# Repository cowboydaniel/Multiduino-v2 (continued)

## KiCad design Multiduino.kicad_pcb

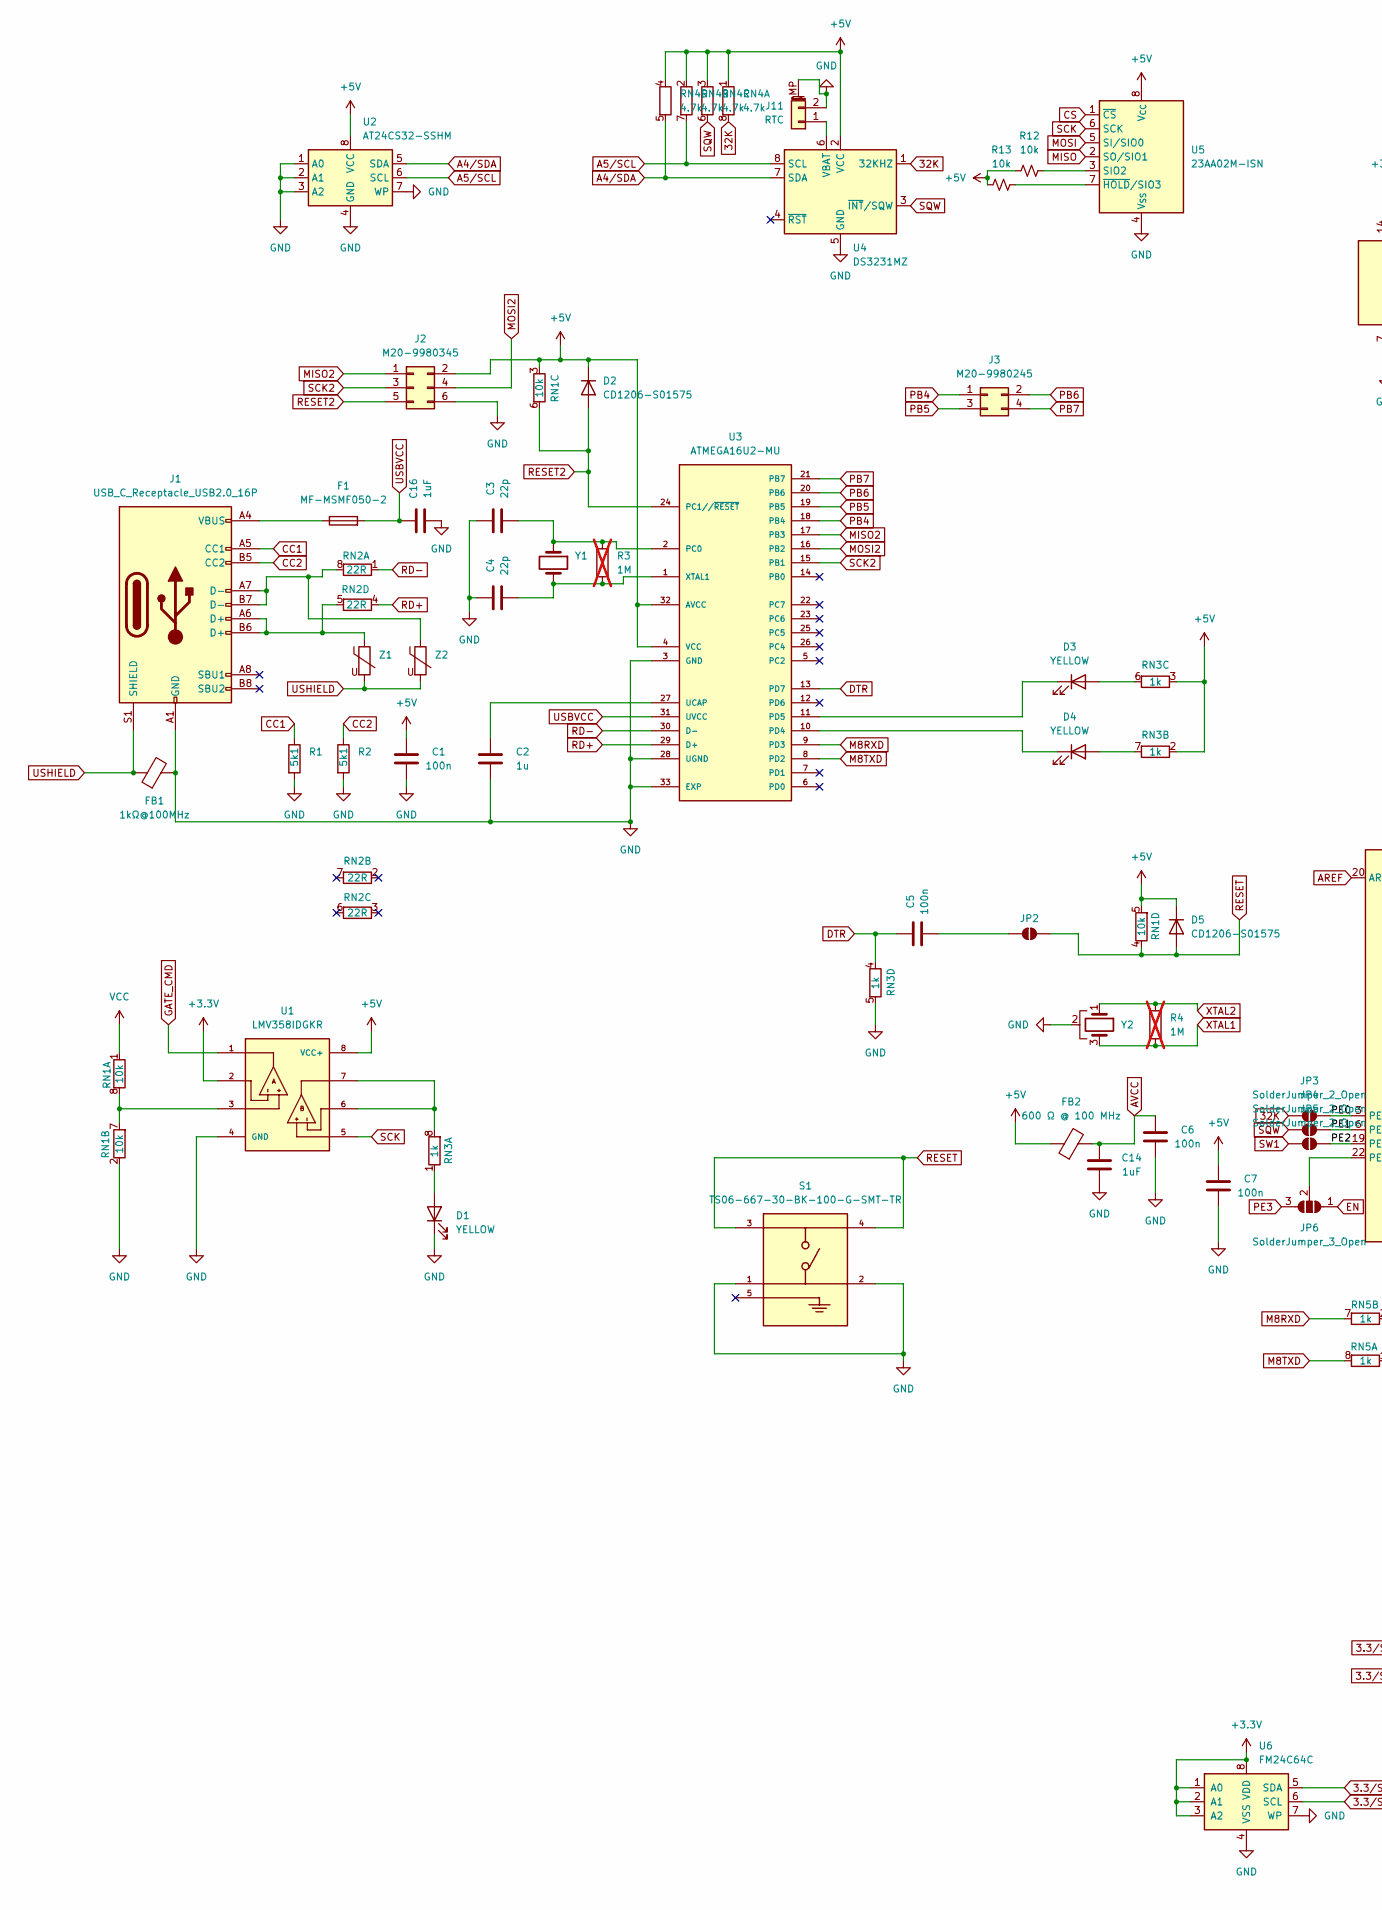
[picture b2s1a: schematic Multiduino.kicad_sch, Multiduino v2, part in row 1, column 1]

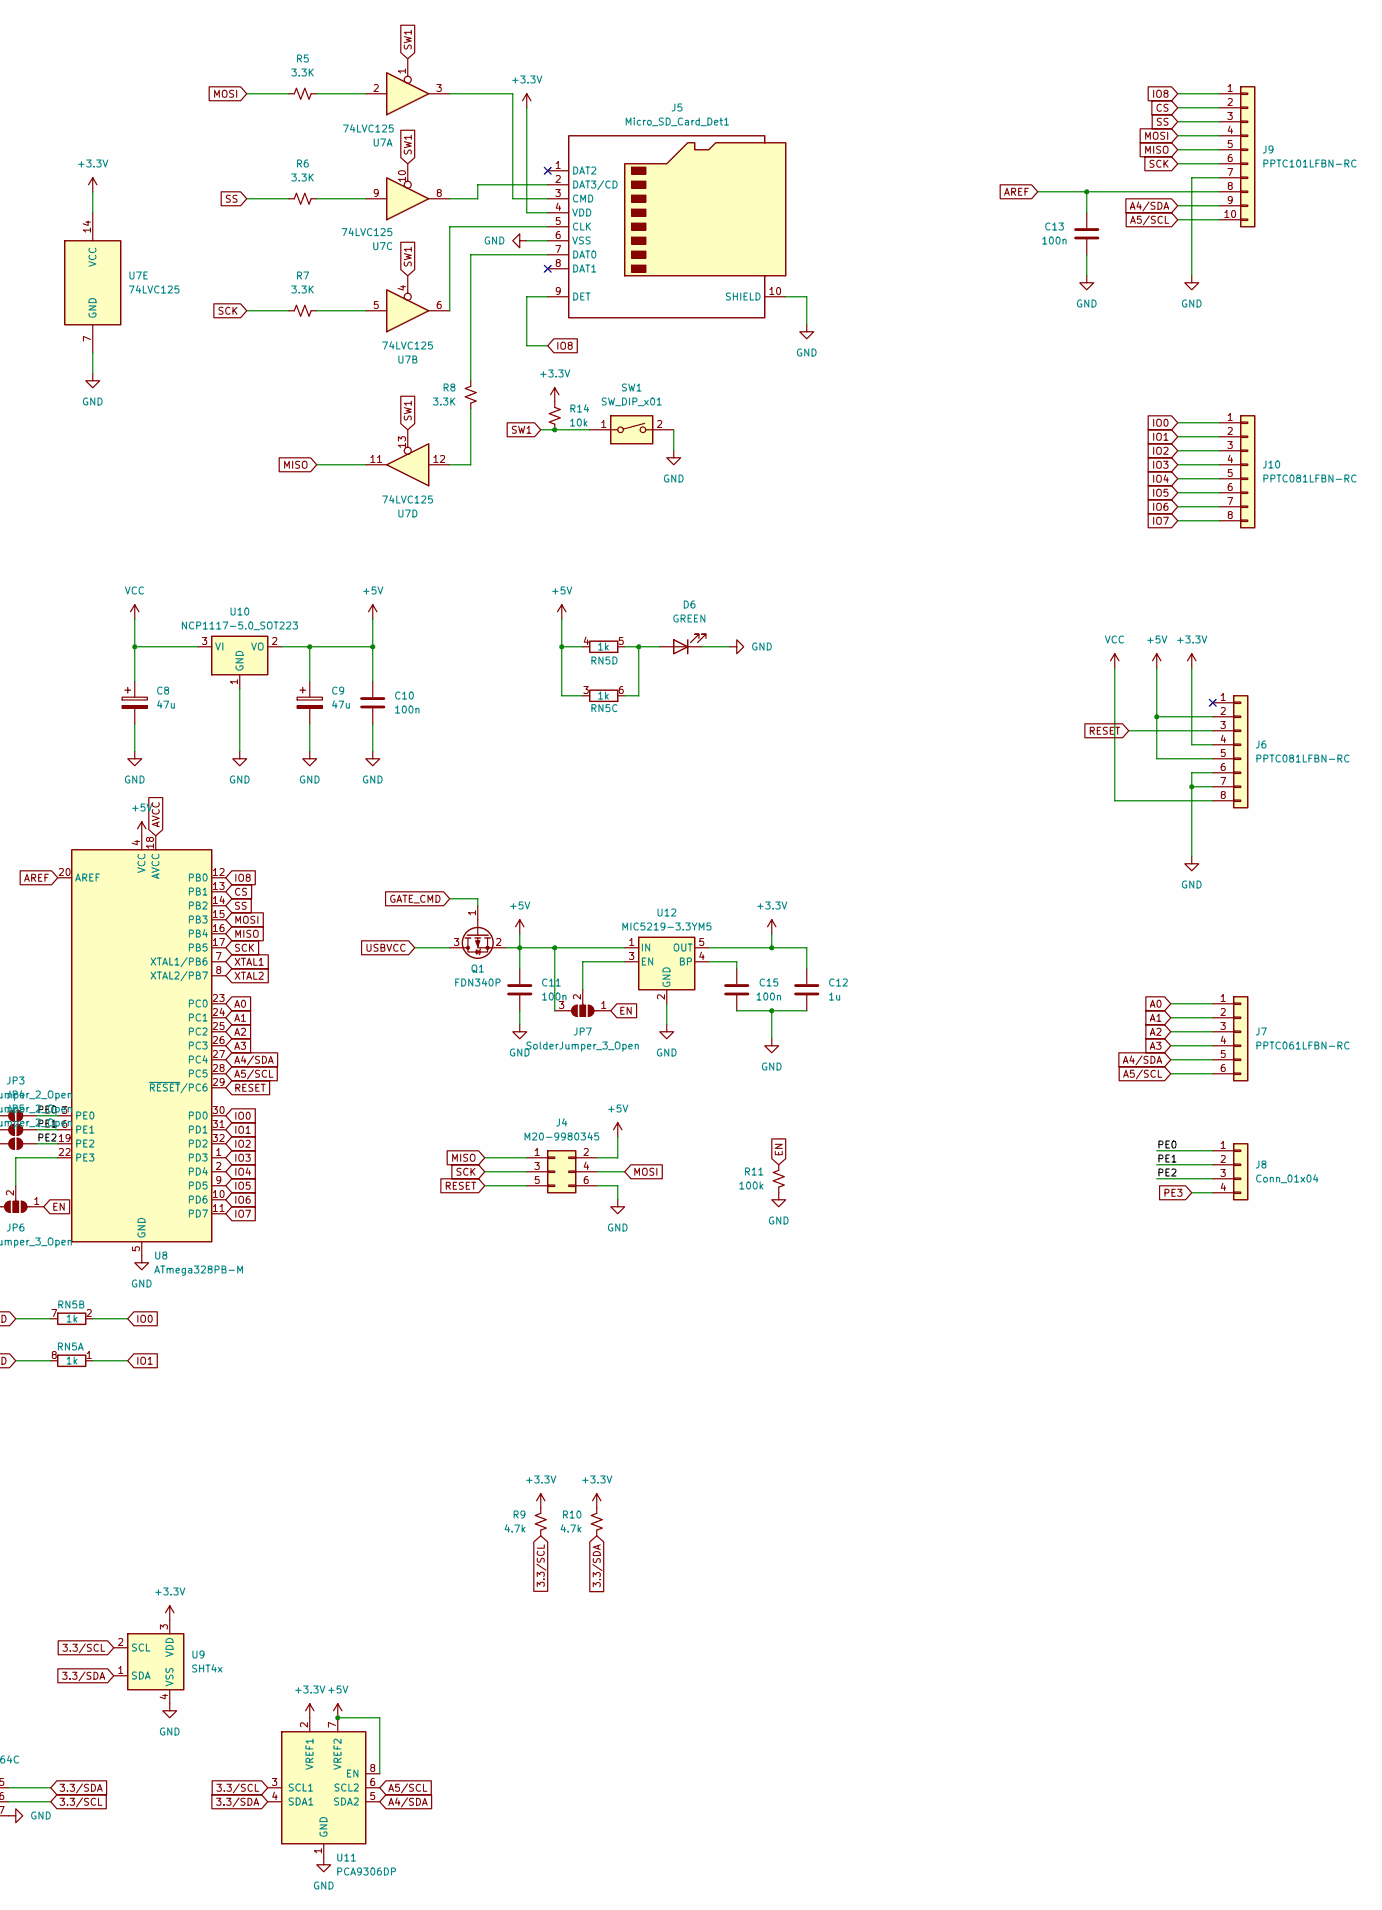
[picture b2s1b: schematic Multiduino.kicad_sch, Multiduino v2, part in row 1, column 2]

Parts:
C1, C5, C6, C7, C10, C11, C13, C15: 100n; C_0603_1608Metric
C2, C12: 1u; C_0603_1608Metric
C3, C4: 22p; C_0603_1608Metric
C8, C9: 47u; CAP_EEHZA1E470P
C14, C16: 1uF; C_0603_1608Metric
D1, D3, D4: YELLOW; LED_0805_2012Metric
D2, D5: CD1206-S01575; D_1206_3216Metric
D6: GREEN; LED_0805_2012Metric
F1: MF-MSMF050-2; Fuse_1812_4532Metric_Pad1.30x3.40mm_HandSolder
FB1: 1kΩ@100MHz; L_0805_2012Metric
FB2: 600 Ω @ 100 MHz; L_0805_2012Metric
J1: USB_C_Receptacle_USB2.0_16P; USB_C_Receptacle_GCT_USB4105-xx-A_16P_TopMnt_Horizontal
J2, J4: M20-9980345; PinHeader_2x03_P2.54mm_Vertical
J3: M20-9980245; CONN_M20-9980245_HRW
J5: Micro_SD_Card_Det1; microSD_HC_Hirose_DM3D-SF
J6, J10: PPTC081LFBN-RC; PinSocket_1x08_P2.54mm_Vertical
J7: PPTC061LFBN-RC; PinSocket_1x06_P2.54mm_Vertical
J8: Conn_01x04; PinSocket_1x04_P2.54mm_Vertical
J9: PPTC101LFBN-RC; PinSocket_1x10_P2.54mm_Vertical
J11: RTC; JST_ACH_BM02B-ACHSS-GAN-ETF_1x02-1MP_P1.20mm_Vertical
JP2: SolderJumper_2_Open; SolderJumper-2_P1.3mm_Open_Pad1.0x1.5mm
JP3, JP4, JP5: SolderJumper_2_Open; SolderJumper-2_P1.3mm_Open_RoundedPad1.0x1.5mm
JP6, JP7: SolderJumper_3_Open; SolderJumper-3_P1.3mm_Open_RoundedPad1.0x1.5mm_NumberLabels
Q1: FDN340P; SC-59
R1, R2: 5k1; R_0603_1608Metric
R3, R4: 1M; R_0603_1608Metric; not fitted
R5, R6, R7, R8: 3.3K; R_0201_0603Metric
R9, R10: 4.7k; R_0201_0603Metric
R11: 100k; R_0201_0603Metric
R12, R13, R14: 10k; R_0201_0603Metric
RN1: 10k; R_Array_Convex_4x0603
RN2: 22R; R_Array_Convex_4x0603
RN3, RN5: 1k; R_Array_Convex_4x0603
RN4: 4.7k; R_Array_Convex_4x0603
S1: TS06-667-30-BK-100-G-SMT-TR; SW_TS06-667-30-BK-100-G-SMT-TR; PARTREV 1.0
SW1: SW_DIP_x01; SW_DIP_SPSTx01_Slide_6.7x4.1mm_W6.73mm_P2.54mm_LowProfile_J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
U1: LMV358IDGKR; MSOP-8_3x3mm_P0.65mm; PARTREV X
U2: AT24CS32-SSHM; SOIC-8_3.9x4.9mm_P1.27mm
U3: ATMEGA16U2-MU; VQFN-32-1EP_5x5mm_P0.5mm_EP3.1x3.1mm
U4: DS3231MZ; SOIC-8_3.9x4.9mm_P1.27mm
U5: 23AA02M-ISN; SOIC-8_3.9x4.9mm_P1.27mm
U6: FM24C64C; SOIC-8_3.9x4.9mm_P1.27mm
U7: 74LVC125; TSSOP-14_4.4x5mm_P0.65mm
U8: ATmega328PB-M; QFN-32-1EP_5x5mm_P0.5mm_EP3.1x3.1mm
U9: SHT4x; Sensirion_DFN-4_1.5x1.5mm_P0.8mm_SHT4x_NoCentralPad
U10: NCP1117-5.0_SOT223; SOT-223-3_TabPin2
U11: PCA9306DP; TSSOP-8_3x3mm_P0.65mm
U12: MIC5219-3.3YM5; SOT-23-5
Y1: LFXTAL003240BULK; Crystal_HC49-4H_Vertical
Y2: CSTNE16M0V530000R0; Resonator_SMD_Murata_CSTxExxV-3Pin_3.0x1.1mm
Z1, Z2: 5pF@1MHz; R_0603_1608Metric

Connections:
3.3/SCL: R9.2, U6.6 (SCL), U9.2 (SCL), U11.3 (SCL1)
3.3/SDA: R10.2, U6.5 (SDA), U9.1 (SDA), U11.4 (SDA1)
32K: JP3.1 (A), RN4.8 (R1.2), U4.1 (32KHZ)
+3.3V: C12.2, J5.4 (VDD), J6.4, R9.1, R10.1, R14.1, U1.2, U6.1 (A0), U6.2 (A1), U6.3 (A2), U6.8 (VDD), U7.14 (VCC), U9.3 (VDD), U11.2 (VREF1), U12.5 (OUT)
+5V: C1.1, C7.2, C9.1, C10.1, C11.2, D2.1 (K), D5.1 (K), FB2.1, J2.2, J4.2, J6.2, J6.5, JP7.3 (B), Q1.2 (S), R12.1, R13.1, RN1.3 (R3.1), RN1.5 (R4.2), RN3.2 (R2.1), RN3.3 (R3.1), RN4.1 (R1.1), RN4.2 (R2.1), RN4.3 (R3.1), RN4.4 (R4.1), RN5.3 (R3.1), RN5.4 (R4.1), U1.8 (VCC+), U2.8 (VCC), U3.4 (VCC), U3.32 (AVCC), U4.2 (VCC), U5.8 (V_{CC}), U8.4 (VCC), U10.2 (VO), U11.7 (VREF2), U11.8 (EN), U12.1 (IN)
/PE0: J8.1, JP3.2 (B), U8.3 (PE0)
/PE1: J8.2, JP4.2 (B), U8.6 (PE1)
/PE2: J8.3, JP5.2 (B), U8.19 (PE2)
A0: J7.1, U8.23 (PC0)
A1: J7.2, U8.24 (PC1)
A2: J7.3, U8.25 (PC2)
A3: J7.4, U8.26 (PC3)
A4/SDA: J7.5, J9.9, RN4.5 (R4.2), U2.5 (SDA), U4.7 (SDA), U8.27 (PC4), U11.5 (SDA2)
A5/SCL: J7.6, J9.10, RN4.7 (R2.2), U2.6 (SCL), U4.8 (SCL), U8.28 (PC5), U11.6 (SCL2)
AREF: C13.1, J9.8, U8.20 (AREF)
AVCC: C6.1, C14.1, FB2.2, U8.18 (AVCC)
CC1: J1.A5 (CC1), R1.1
CC2: J1.B5 (CC2), R2.1
CS: J9.2, U5.1 (~CS), U8.13 (PB1)
DTR: C5.1, RN3.4 (R4.1), U3.13 (PD7)
EN: JP6.1 (A), JP7.1 (A), R11.1
GATE_CMD: Q1.1 (G), U1.1
GND: C1.2, C2.1, C3.2, C4.2, C6.2, C7.1, C8.2, C9.2, C10.2, C11.1, C12.1, C13.2, C14.2, C15.2, C16.1, D1.1 (K), D6.1 (K), FB1.2, J1.A1 (GND), J1.A12 (GND), J1.B1 (GND), J1.B12 (GND), J2.6, J4.6, J5.6 (VSS), J5.10 (SHIELD), J6.6, J6.7, J9.7, J11.2, J11.MP (MountPin), R1.2, R2.2, R11.2, RN1.2 (R2.1), RN3.5 (R4.2), S1.1, S1.2, SW1.2, U1.4 (GND), U2.1 (A0), U2.2 (A1), U2.3 (A2), U2.4 (GND), U2.7 (WP), U3.3 (GND), U3.28 (UGND), U3.33 (EXP), U4.5 (GND), U5.4 (V_{SS}), U6.4 (VSS), U6.7 (WP), U7.7 (GND), U8.5 (GND), U8.21 (GND), U8.33 (GND), U9.4 (VSS), U10.1 (GND), U11.1 (GND), U12.2 (GND), Y2.2
IO0: J10.1, RN5.2 (R2.1), U8.30 (PD0)
IO1: J10.2, RN5.1 (R1.1), U8.31 (PD1)
IO2: J10.3, U8.32 (PD2)
IO3: J10.4, U8.1 (PD3)
IO4: J10.5, U8.2 (PD4)
IO5: J10.6, U8.9 (PD5)
IO6: J10.7, U8.10 (PD6)
IO7: J10.8, U8.11 (PD7)
IO8: J5.9 (DET), J9.1, U8.12 (PB0)
M8RXD: RN5.7 (R2.2), U3.9 (PD3)
M8TXD: RN5.8 (R1.2), U3.8 (PD2)
MISO: J4.1, J9.5, U5.2 (SO/SIO1), U7.11, U8.16 (PB4)
MISO2: J2.1, U3.17 (PB3)
MOSI: J4.4, J9.4, R5.1, U5.5 (SI/SIO0), U8.15 (PB3)
MOSI2: J2.4, U3.16 (PB2)
unnamed: D1.2 (A), RN3.1 (R1.1)
unnamed: D3.2 (A), RN3.6 (R3.2)
unnamed: D3.1 (K), U3.11 (PD5)
unnamed: D4.2 (A), RN3.7 (R2.2)
unnamed: D4.1 (K), U3.10 (PD4)
unnamed: D6.2 (A), RN5.5 (R4.2), RN5.6 (R3.2)
unnamed: F1.1, J1.A4 (VBUS), J1.A9 (VBUS), J1.B4 (VBUS), J1.B9 (VBUS)
unnamed: J5.5 (CLK), U7.6
unnamed: J5.3 (CMD), U7.3
unnamed: J5.7 (DAT0), R8.1
unnamed: J5.2 (DAT3/CD), U7.8
unnamed: J11.1, U4.6 (VBAT)
unnamed: C5.2, JP2.1 (A)
unnamed: JP6.2 (C), U8.22 (PE3)
unnamed: JP7.2 (C), U12.3 (EN)
unnamed: R5.2, U7.2
unnamed: R6.2, U7.9
unnamed: R7.2, U7.5
unnamed: R8.2, U7.12
unnamed: RN1.7 (R2.2), RN1.8 (R1.2), U1.3
unnamed: J1.A7 (D-), J1.B7 (D-), RN2.8 (R1.2), Z2.1
unnamed: J1.A6 (D+), J1.B6 (D+), RN2.5 (R4.2), Z1.1
unnamed: RN3.8 (R1.2), U1.6, U1.7
unnamed: C3.1, R3.1, U3.2 (PC0), Y1.1
unnamed: C2.2, U3.27 (UCAP)
unnamed: C4.1, R3.2, U3.1 (XTAL1), Y1.2
unnamed: R12.2, U5.3 (SIO2)
unnamed: R13.2, U5.7 (~HOLD/SIO3)
unnamed: C15.1, U12.4 (BP)
PB4: J3.1, U3.18 (PB4)
PB5: J3.3, U3.19 (PB5)
PB6: J3.2, U3.20 (PB6)
PB7: J3.4, U3.21 (PB7)
PE3: J8.4, JP6.3 (B)
RD+: RN2.4 (R4.1), U3.29 (D+)
RD-: RN2.1 (R1.1), U3.30 (D-)
RESET: D5.2 (A), J4.5, J6.3, JP2.2 (B), RN1.4 (R4.1), S1.3, S1.4, U8.29 (~RESET/PC6)
RESET2: D2.2 (A), J2.5, RN1.6 (R3.2), U3.24 (PC1//~RESET)
SCK: J4.3, J9.6, R7.1, U1.5, U5.6 (SCK), U8.17 (PB5)
SCK2: J2.3, U3.15 (PB1)
SQW: JP4.1 (A), RN4.6 (R3.2), U4.3 (~INT/SQW)
SS: J9.3, R6.1, U8.14 (PB2)
SW1: JP5.1 (A), R14.2, SW1.1, U7.1, U7.4, U7.10, U7.13
USBVCC: C16.2, F1.2, Q1.3 (D), U3.31 (UVCC)
USHIELD: FB1.1, J1.S1 (SHIELD), Z1.2, Z2.2
VCC: C8.1, J6.8, RN1.1 (R1.1), U10.3 (VI)
XTAL1: R4.2, U8.7 (XTAL1/PB6), Y2.3
XTAL2: R4.1, U8.8 (XTAL2/PB7), Y2.1

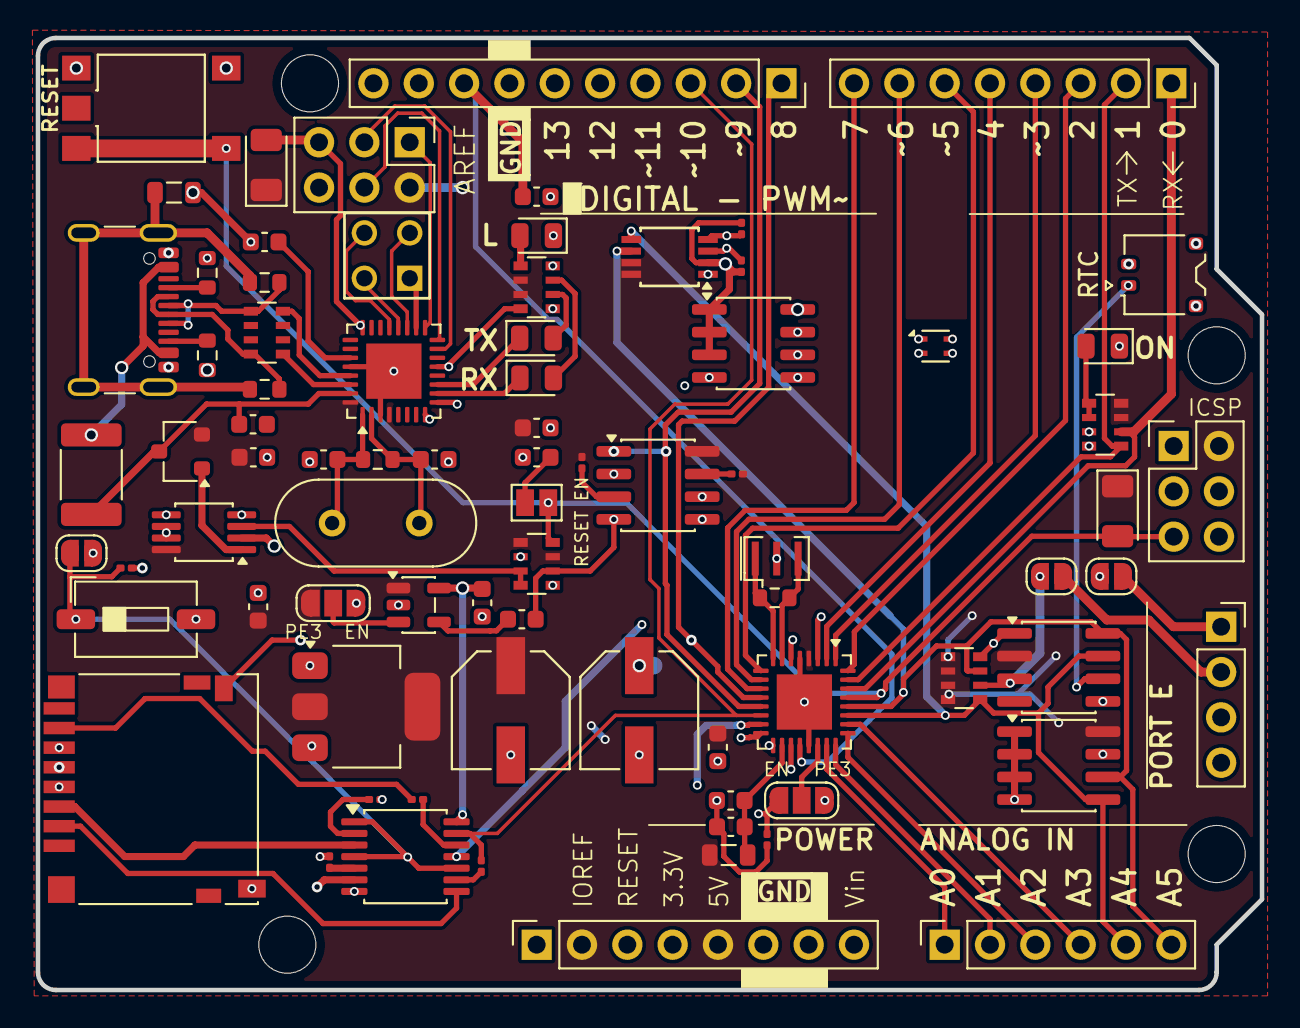
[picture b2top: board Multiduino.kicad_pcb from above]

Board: 4 copper layers, 68.6 x 53.3 mm, 80 parts (0 on the bottom side), 86 nets.

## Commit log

2026-02-18 Revise README for Multiduino v2
    Updated README to enhance clarity and detail about the Multiduino v2 features and usage.
2026-02-18 Enhance ATmega328PB description in README
    Updated description of the ATmega328PB processor for clarity and detail.
2026-02-18 Add license, gitignore, and core folder structure
    - Add CERN-OHL-W-2.0 license
    - Add .gitignore for KiCad, Arduino build artifacts, and OS/editor files
    - Add core/ subfolder with a basic README for the Arduino IDE core
    https://claude.ai/code/session_01TigvJw977raWhsh9P7WbVi
2026-02-18 Fix core links in README to point to core/ subfolder
    https://claude.ai/code/session_01TigvJw977raWhsh9P7WbVi
2026-02-18 Add initial Arduino core files for Multiduino v2
    - boards.txt: ATmega328PB at 16MHz, Optiboot bootloader, avrdude upload
    - platform.txt: AVR toolchain configuration
    - variants/multiduino_v2/pins_arduino.h: full pin mapping for D0-D23
    Pin assignments verified against Multiduino.net (KiCad netlist):
    SRAM CS → D9 / PB1 (net CS)
    SD CS → D10 / PB2 (net SS, via 74LVC125 buffer U7)
2026-02-18 Update core links to outback-arduino-avr repo and remove core/ subdirectory
    Replace local ./core/ links in README.md with the external repository URL
    https://github.com/cowboydaniel/outback-arduino-avr, and delete the core/
    subdirectory from the project.
    https://claude.ai/code/session_01JpdCYsrmnwNKwNi9Egxcex
2026-06-09 Update Multiduino v2 design
